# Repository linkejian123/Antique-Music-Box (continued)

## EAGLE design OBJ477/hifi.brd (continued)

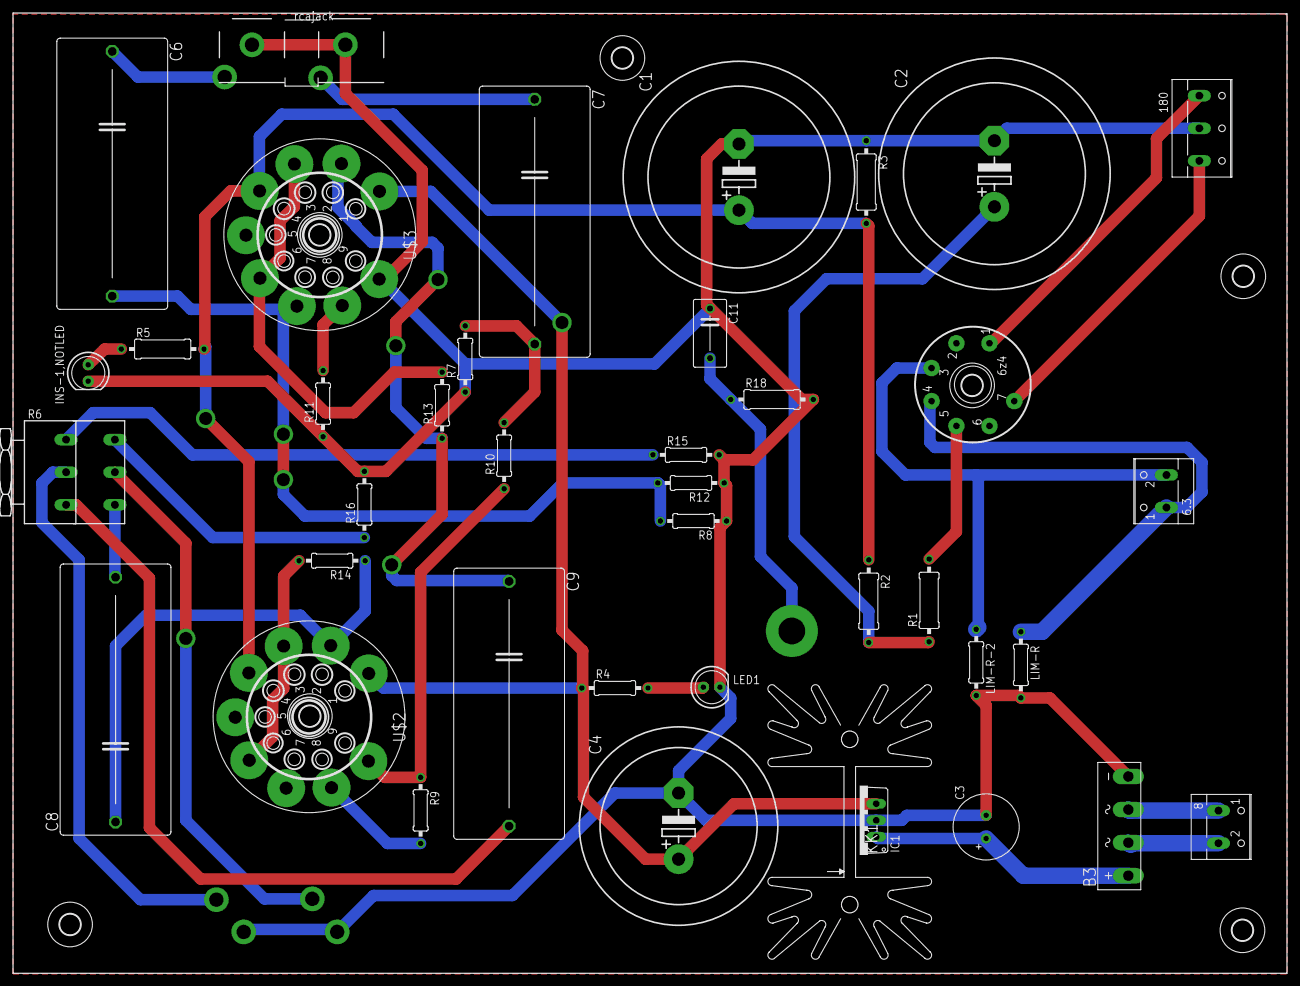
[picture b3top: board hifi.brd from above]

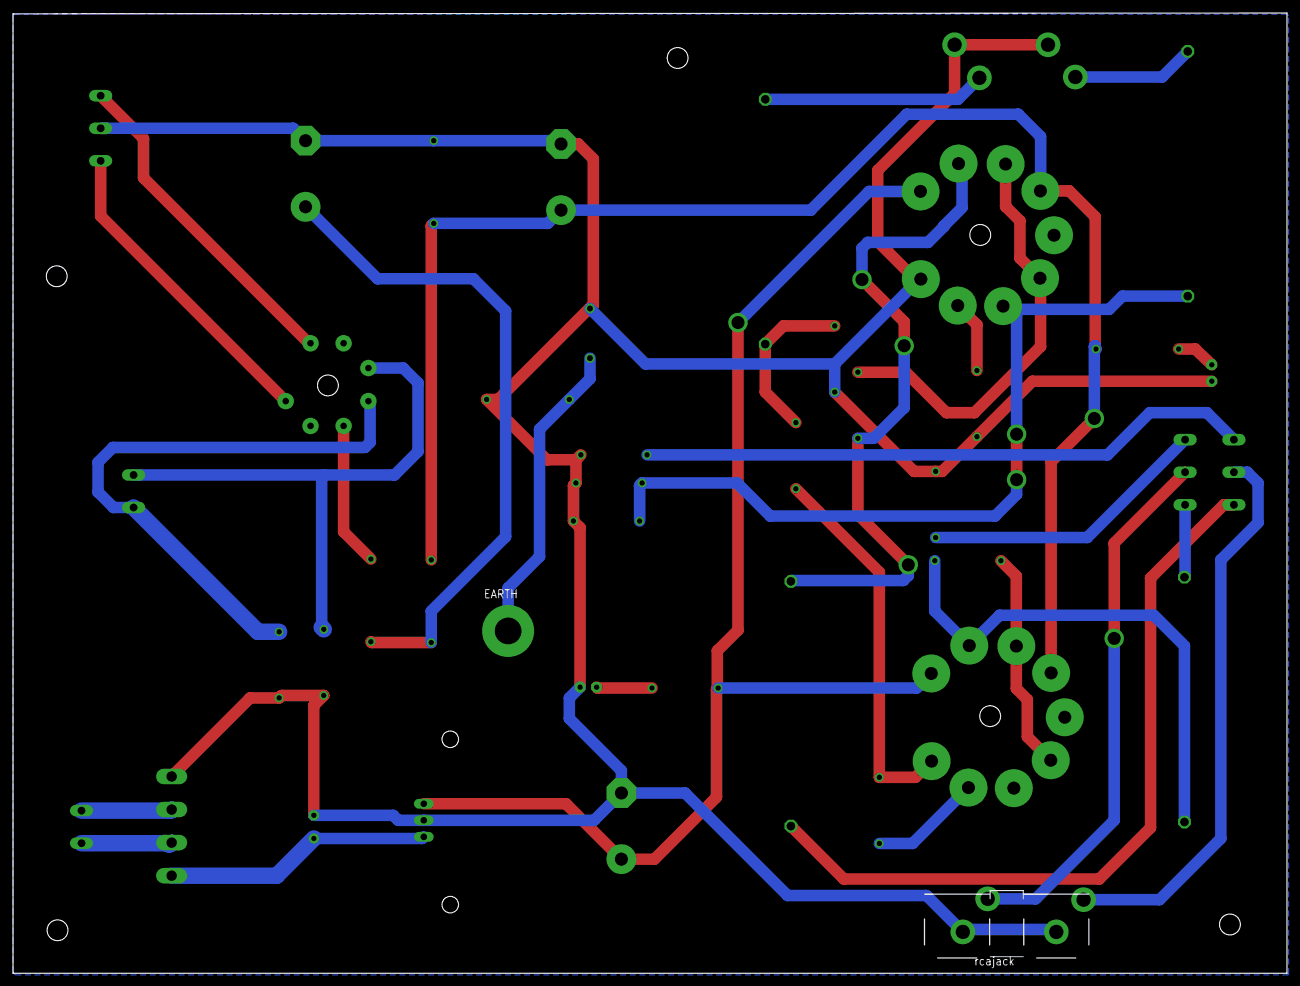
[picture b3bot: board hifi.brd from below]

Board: 2 copper layers, 195.7 x 147.5 mm, 49 parts (2 on the bottom side), 32 nets.

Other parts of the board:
U$6, U$7, U$8, U$9, U$10, U$11, U$12: 3,2

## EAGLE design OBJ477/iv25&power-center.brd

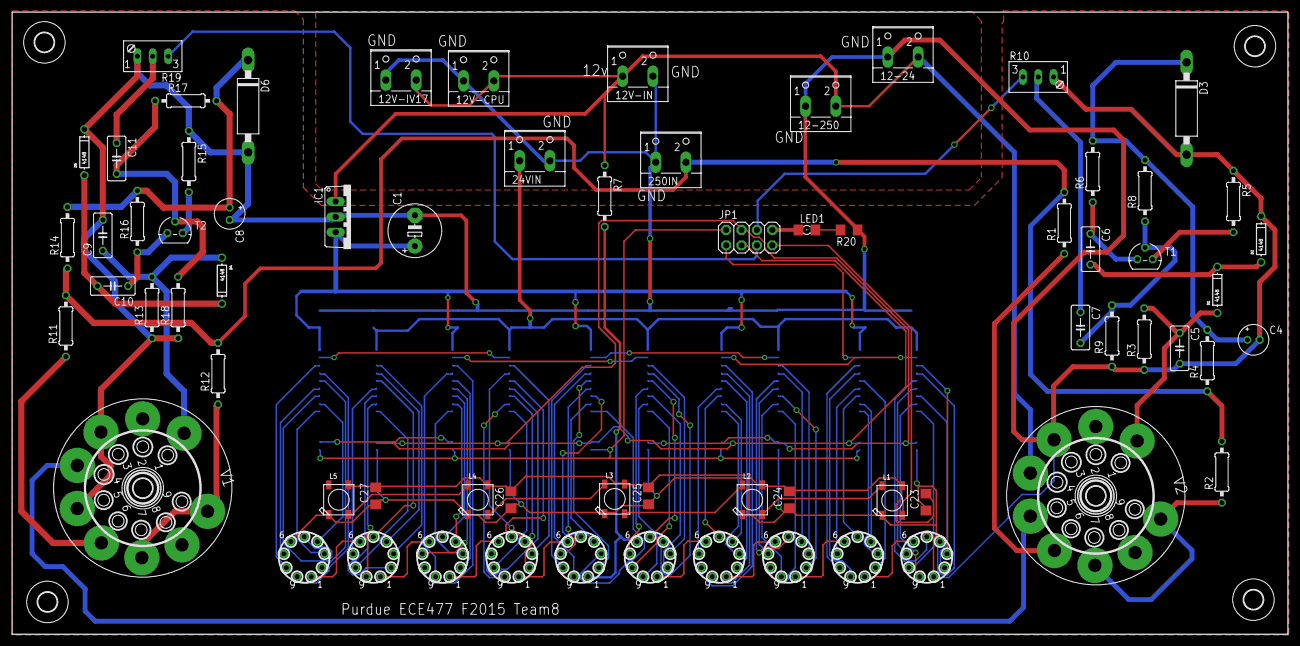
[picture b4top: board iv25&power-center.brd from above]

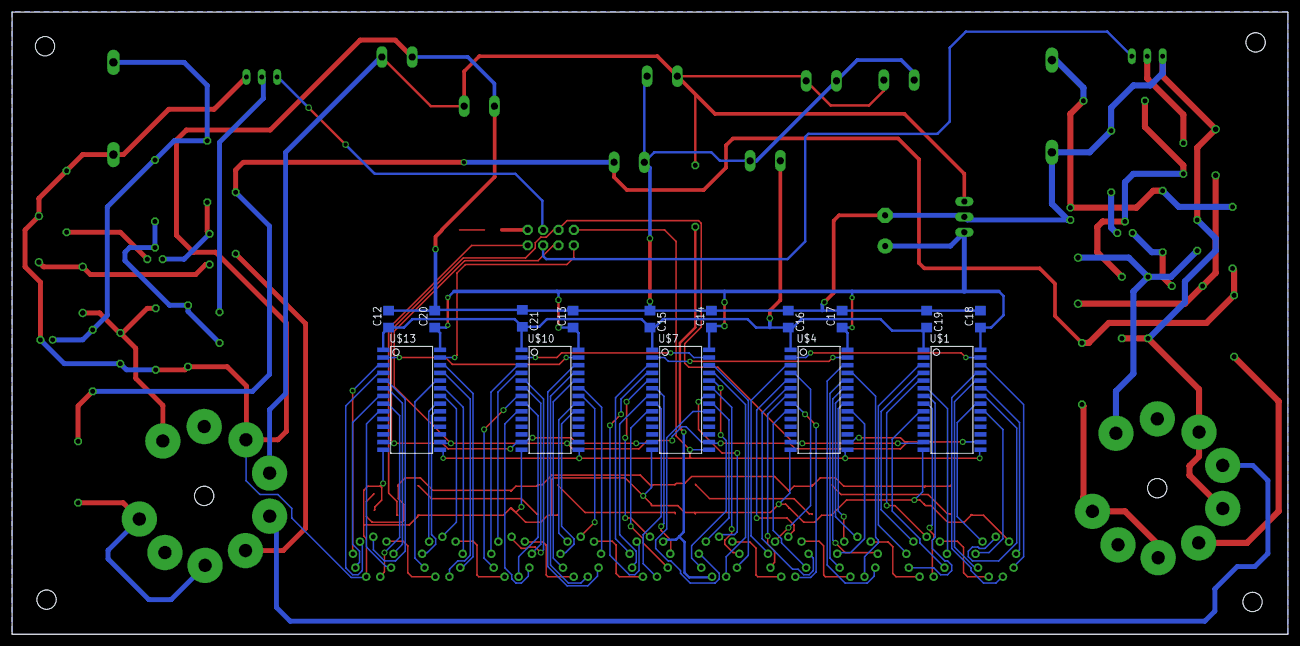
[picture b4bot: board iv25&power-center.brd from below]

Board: 2 copper layers, 210.8 x 102.8 mm, 90 parts (15 on the bottom side), 121 nets.

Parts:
12-24, 12-250, 12V-CPU, 12V-IN, 12V-IV17, 24VIN, 250IN: W237-102
C1: E5-8,5
C4, C8: 10uf/35v; E2-5
C5, C6, C7, C9, C10, C11: 100NF; C050-030X075
C12, C13, C14, C15, C16, C17, C18, C19, C20, C21: 100nf; C1206
C23, C24, C25, C26, C27: C1206
D1, D2, D4, D5: 4148; DO-1N4148
D3, D6: Z-30V; C1702-15
IC1: 7805TV; TO220V
JP1: 2X04
L1, L2, L3, L4, L5: WS2812B
LED1: 1206
R1, R11: 10k; 0207/10
R2, R12: 470k; 0207/10
R3, R8, R13, R17: 1M; 0207/10
R4, R14: 100k/1w; 0207/10
R5, R15: 2.7K; 0207/10
R6, R16: 47K; 0207/10
R7: 20ohm; 0207/10
R9, R18: 56K; 0207/10
R10, R19: 100K; S64W
R20: R1206
T1, T2: BC546; TO92
U$1, U$4, U$7, U$10, U$13: MAX6921; SOIC-28W
U$2, U$3, U$5, U$6, U$8, U$9, U$11, U$12, U$14, U$15: IV25; NIXIE-9
U$16, U$17, U$18, U$19, U$20, U$21: 3,2
V1, V2: NOVAL

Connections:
5VDC: C1.+, C13.1, C14.1, C17.1, C18.1, C20.1, IC1.3, U$1.28, U$4.28, U$7.28, U$10.28, U$13.28
12VDC: 12-24.2, 12-250.2, 12V-CPU.2, 12V-IN.1, 12V-IV17.2, IC1.1, R7.1, V2.4
24VDC: 24VIN.1, C12.1, C15.2, C16.2, C19.2, C21.2, U$1.1, U$4.1, U$7.1, U$10.1, U$13.1
+5V: C23.2, C24.2, C25.2, C26.2, C27.2, L1.1-VDD, L2.1-VDD, L3.1-VDD, L4.1-VDD, L5.1-VDD
AGND: 12-24.1, 12-250.1, 12V-CPU.1, 12V-IN.2, 12V-IV17.1, 24VIN.2, 250IN.1, C1.-, C4.-, C5.2, C8.-, C9.2, C12.2, C13.2, C14.2, C15.1, C16.1, C17.2, C18.2, C19.1, C20.2, C21.1, C23.1, C24.1, C25.1, C26.1, C27.1, D2.C, D3.A, D5.C, D6.A, IC1.2, L1.3-GND, L2.3-GND, L3.3-GND, L4.3-GND, L5.3-GND, R3.1, R5.1, R9.1, R10.A, R13.1, R15.1, R18.1, R19.A, R20.1, U$1.14, U$2.6, U$4.14, U$7.14, U$10.14, U$13.14, U$15.1, V1.3, V1.5, V2.3
AUDIO-L: JP1.5, R19.E
AUDIO-R: JP1.6, R10.E
BLANK: JP1.4, U$1.13, U$4.13, U$7.13, U$10.13, U$13.13
CLOCK: JP1.2, U$1.15, U$4.15, U$7.15, U$10.15, U$13.15
DATA: JP1.1, U$13.27
LED-DATA: JP1.7, L1.4-DIN
LOAD: JP1.3, U$1.16, U$4.16, U$7.16, U$10.16, U$13.16
unnamed: U$1.24, U$2.2
unnamed: U$1.20, U$2.3
unnamed: U$1.21, U$2.4
unnamed: U$1.22, U$2.5
unnamed: U$1.23, U$2.7
unnamed: U$1.26, U$2.8
unnamed: U$1.25, U$2.9
unnamed: U$1.7, U$3.2
unnamed: U$1.3, U$3.3
unnamed: U$1.4, U$3.4
unnamed: U$1.5, U$3.5
unnamed: U$1.6, U$3.7
unnamed: U$1.9, U$3.8
unnamed: U$1.8, U$3.9
unnamed: L1.2-DOUT, L2.4-DIN
unnamed: U$4.24, U$5.2
unnamed: LED1.C, R20.2
unnamed: U$4.20, U$5.3
unnamed: U$4.21, U$5.4
unnamed: U$4.22, U$5.5
unnamed: U$4.23, U$5.7
unnamed: U$4.26, U$5.8
unnamed: U$4.25, U$5.9
unnamed: U$4.7, U$6.2
unnamed: U$4.3, U$6.3
unnamed: U$4.4, U$6.4
unnamed: U$4.5, U$6.5
unnamed: U$4.6, U$6.7
unnamed: U$4.9, U$6.8
unnamed: U$4.8, U$6.9
unnamed: U$7.24, U$8.2
unnamed: U$7.20, U$8.3
unnamed: L2.2-DOUT, L3.4-DIN
unnamed: U$7.21, U$8.4
unnamed: U$7.22, U$8.5
unnamed: U$1.27, U$4.2
unnamed: U$7.23, U$8.7
unnamed: U$7.26, U$8.8
unnamed: U$7.25, U$8.9
unnamed: U$7.7, U$9.2
unnamed: U$7.3, U$9.3
unnamed: U$7.4, U$9.4
unnamed: U$7.5, U$9.5
unnamed: U$7.6, U$9.7
unnamed: U$7.9, U$9.8
unnamed: U$7.8, U$9.9
unnamed: U$10.24, U$11.2
unnamed: U$10.20, U$11.3
unnamed: U$10.21, U$11.4
unnamed: U$10.22, U$11.5
unnamed: L3.2-DOUT, L4.4-DIN
unnamed: U$10.23, U$11.7
unnamed: U$10.26, U$11.8
unnamed: U$4.27, U$7.2
unnamed: U$10.25, U$11.9
unnamed: U$10.7, U$12.2
unnamed: U$10.3, U$12.3
unnamed: U$10.4, U$12.4
unnamed: U$10.5, U$12.5
unnamed: U$10.6, U$12.7
unnamed: U$10.9, U$12.8
unnamed: U$10.8, U$12.9
unnamed: U$13.24, U$14.2
unnamed: U$13.20, U$14.3
unnamed: U$13.21, U$14.4
unnamed: U$13.22, U$14.5
unnamed: U$13.23, U$14.7
unnamed: U$13.26, U$14.8
unnamed: L4.2-DOUT, L5.4-DIN
unnamed: U$13.25, U$14.9
unnamed: U$13.7, U$15.2
unnamed: U$13.3, U$15.3
unnamed: U$13.4, U$15.4
unnamed: U$13.5, U$15.5
unnamed: U$13.6, U$15.7
unnamed: U$13.9, U$15.8
unnamed: U$13.8, U$15.9
unnamed: U$2.1, U$3.6
unnamed: U$3.1, U$5.6
unnamed: U$5.1, U$6.6
unnamed: U$6.1, U$8.6
unnamed: U$14.1, U$15.6
unnamed: U$12.1, U$14.6
unnamed: U$11.1, U$12.6
unnamed: U$9.1, U$11.6
unnamed: R7.2, U$8.1, U$9.6
unnamed: C10.2, D4.C, D5.A
unnamed: C6.2, D1.C, D2.A
unnamed: C6.1, R6.1, T1.3
unnamed: V1.4, V2.5
unnamed: R2.1, V2.7, V2.9
unnamed: R1.1, V2.6
unnamed: C5.1, D1.A, R3.2, V2.1
unnamed: C4.+, D3.C, R4.2, R6.2, R8.2
unnamed: R5.2, T1.1
unnamed: 250IN.2, R1.2, R2.2, R4.1, R11.2, R12.2, R14.1
unnamed: R12.1, V1.7, V1.9
unnamed: R11.1, V1.6
unnamed: C7.2, R8.1, R9.2, T1.2
unnamed: C9.1, D4.A, R13.2, V1.1
unnamed: C7.1, R10.S
unnamed: C8.+, D6.C, R14.2, R16.2, R17.2
unnamed: C10.1, R16.1, T2.3
unnamed: R15.2, T2.1
unnamed: C11.2, R17.1, R18.2, T2.2
unnamed: C11.1, R19.S
unnamed: U$10.27, U$13.2
unnamed: U$7.27, U$10.2
unnamed: JP1.8, LED1.A

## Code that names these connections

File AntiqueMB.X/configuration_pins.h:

/* 
 * File:   configuration_pins.h
 * Author: EE63PC9-user
 *
 * Created on November 22, 2015, 4:04 PM
 */

#ifndef CONFIGURATION_PINS_H
#define	CONFIGURATION_PINS_H

#ifdef	__cplusplus
extern "C" {
    

#endif

#define OUTPUT 0
#define INPUT 1

//VFD Display configuration    
#define TRIS_VFD_LATCH  TRISFbits.TRISF4    // RF4 latch pin
#define TRIS_VFD_CLOCK  TRISAbits.TRISA1    // RA1 clock pin
#define TRIS_VFD_DATA  TRISAbits.TRISA2     // RA2 data pin
#define TRIS_VFD_BLANK  TRISGbits.TRISG2    // RG2 blank

#define VFD_LATCH   PORTFbits.RF4
#define VFD_CLOCK   PORTAbits.RA1
#define VFD_DATA   PORTAbits.RA2
#define VFD_BLANK   PORTGbits.RG2
    
// Bar Display configuration
#define TRIS_BAR_LATCH  TRISAbits.TRISA6  // RA6 latch pin
#define TRIS_BAR_CLOCK  TRISFbits.TRISF5  // RF5 clock pin
#define TRIS_BAR_DATA  TRISGbits.TRISG3  // RG3 data pin
#define TRIS_BAR_BLANK  TRISAbits.TRISA7  // RA7 blank
    
#define BAR_LATCH   LATAbits.LATA6
#define BAR_CLOCK   LATFbits.LATF5
#define BAR_DATA   LATGbits.LATG3
#define BAR_BLANK   LATAbits.LATA7
    
// MUX configuration
#define config_mux1 TRISEbits.TRISE1    //mux1
#define config_mux2 TRISDbits.TRISD13   //mux2

#define mux1 PORTEbits.RE1
#define mux2 PORTDbits.RD13
    
// LED configuration
#define TRIS_LED_BAR TRISDbits.TRISD4
#define TRIS_LED_VFD TRISDbits.TRISD5
    
#define LED_BAR PORTDbits.RD4//LATDbits.LATD4
#define LED_VFD PORTDbits.RD5//LATDbits.LATD5
    
void Configure_Pins(void);

#ifdef	__cplusplus
}
#endif

#endif	/* CONFIGURATION_PINS_H */

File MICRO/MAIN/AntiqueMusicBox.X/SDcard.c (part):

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#define R1_PARAMETER        (1<<6)  // The command's argument (e.g. address, block length) was out of the allowed range for this card.

//ports
/*#define LED PORTCbits.RC3           //GPIO
#define LED_DIR TRISCbits.TRISC3 */
#define SD_CS PORTCbits.RC1
#define SD_CS_DIR TRISCbits.TRISC1
#define SDI PORTGbits.RG8
#define SDI_DIR TRISGbits.TRISG8
#define SCK PORTGbits.RG6
#define SCK_DIR TRISGbits.TRISG6
#define SDO PORTGbits.RG7
#define SDO_DIR TRISGbits.TRISG7
#define SD_Enable() SD_CS = 0 
#define SD_Disable() SD_CS = 1 
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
